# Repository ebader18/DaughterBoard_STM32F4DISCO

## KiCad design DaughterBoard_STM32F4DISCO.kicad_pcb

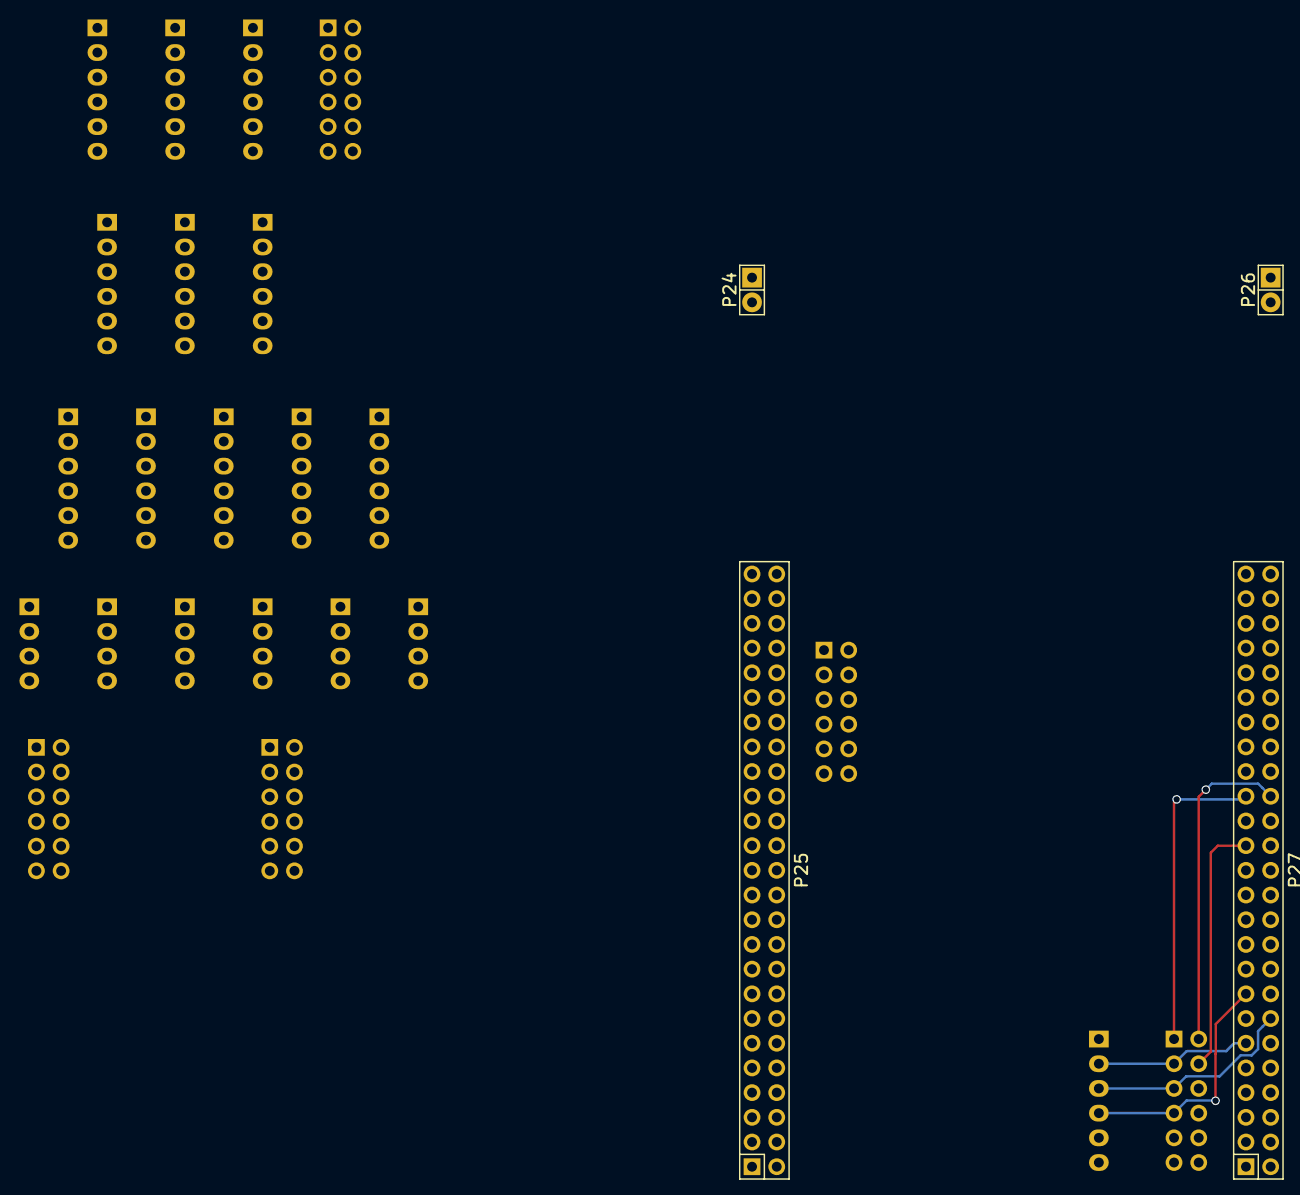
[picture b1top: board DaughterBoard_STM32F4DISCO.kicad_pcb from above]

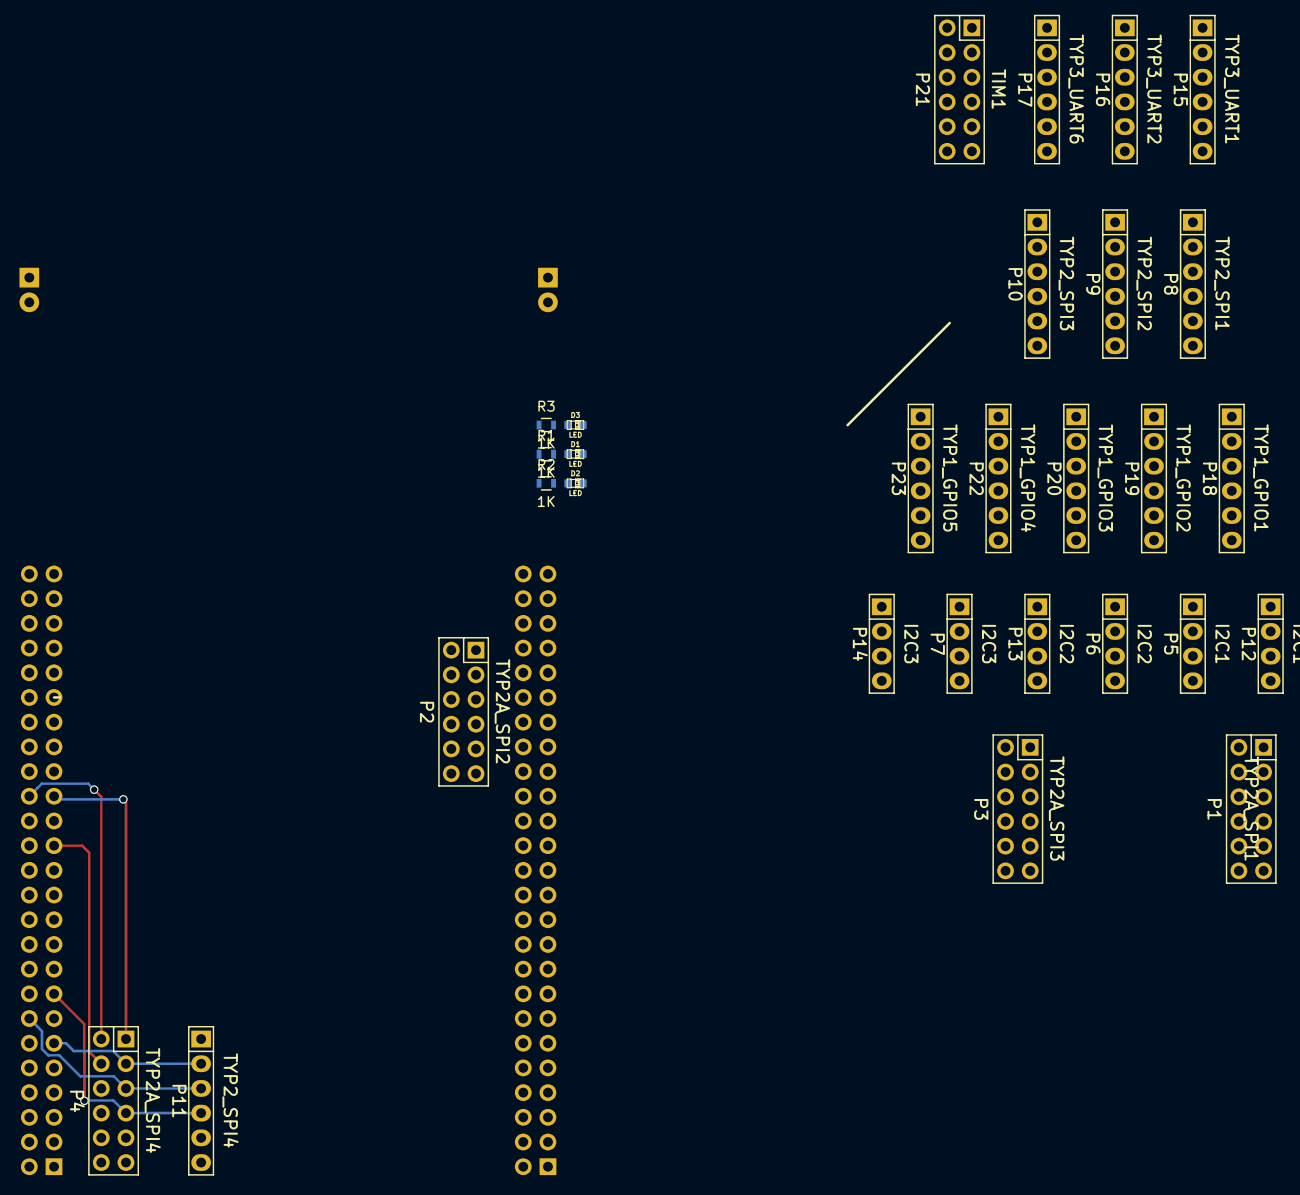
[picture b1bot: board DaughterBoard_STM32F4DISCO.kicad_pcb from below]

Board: 2 copper layers, 33 parts (29 on the bottom side), 77 nets.

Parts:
D1, D2, D3: LED; LED-0603
P1: TYP2A_SPI1; Socket_Strip_Straight_2x06
P2: TYP2A_SPI2; Socket_Strip_Straight_2x06
P3: TYP2A_SPI3; Socket_Strip_Straight_2x06
P4: TYP2A_SPI4; Socket_Strip_Straight_2x06
P5, P12: I2C1; Socket_Strip_Straight_1x04
P6, P13: I2C2; Socket_Strip_Straight_1x04
P7, P14: I2C3; Socket_Strip_Straight_1x04
P8: TYP2_SPI1; Socket_Strip_Straight_1x06
P9: TYP2_SPI2; Socket_Strip_Straight_1x06
P10: TYP2_SPI3; Socket_Strip_Straight_1x06
P11: TYP2_SPI4; Socket_Strip_Straight_1x06
P15: TYP3_UART1; Socket_Strip_Straight_1x06
P16: TYP3_UART2; Socket_Strip_Straight_1x06
P17: TYP3_UART6; Socket_Strip_Straight_1x06
P18: TYP1_GPIO1; Socket_Strip_Straight_1x06
P19: TYP1_GPIO2; Socket_Strip_Straight_1x06
P20: TYP1_GPIO3; Socket_Strip_Straight_1x06
P21: TIM1; Socket_Strip_Straight_2x06
P22: TYP1_GPIO4; Socket_Strip_Straight_1x06
P23: TYP1_GPIO5; Socket_Strip_Straight_1x06
P24, P26: CONN_01X02; Socket_Strip_Straight_1x02
P25, P27: CONN_02X25; Socket_Strip_Straight_2x25
R1, R2, R3: 1K; R_0603

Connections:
/3V: P1.11, P1.12, P2.11, P2.12, P3.11, P3.12, P4.11, P4.12, P5.4, P6.4, P7.4, P8.6, P9.6, P10.6, P11.6, P12.4, P13.4, P14.4, P15.6, P16.6, P17.6, P18.6, P19.6, P20.6, P21.11, P21.12, P22.6, P23.6, P27.5, P27.6, R2.1
/5V: P27.3, P27.4, R1.1
/GND: D1.2, D2.2, D3.2, P1.9, P1.10, P2.9, P2.10, P3.9, P3.10, P4.9, P4.10, P5.3, P6.3, P7.3, P8.5, P9.5, P10.5, P11.5, P12.3, P13.3, P14.3, P15.5, P16.5, P17.5, P18.5, P19.5, P20.5, P21.9, P21.10, P22.5, P23.5, P24.1, P24.2, P25.1, P25.2, P25.5, P25.23, P25.49, P25.50, P26.1, P26.2, P27.1, P27.2, P27.49, P27.50
/PA0: P18.1, P25.12
/PA1: P18.2, P25.11
/PA2: P18.3, P25.14
/PA3: P18.4, P25.13
/PA4: P19.1, P25.16
/PA5: P1.7, P8.4, P25.15
/PA6: P1.5, P8.3, P25.18
/PA7: P19.2, P25.17
/PA8: P7.1, P14.1, P27.43
/PA9: P15.4, P27.44
/PA10: P15.3, P27.41
/PB0: P19.3, P25.22
/PB1: P19.4, P25.21
/PB3: P6.2, P13.2, P27.28
/PB5: P1.3, P8.2, P27.26
/PB6: P23.4, P27.23
/PB7: P1.6, P27.24
/PB8: P5.1, P12.1, P27.19
/PB9: P5.2, P12.2, P27.20
/PB10: P6.1, P13.1, P25.34
/PB12: P11.1, P25.36
/PB13: P2.7, P9.4, P25.37
/PB14: P2.5, P9.3, P25.38
/PB15: P2.3, P9.2
/PC0: P20.1, P25.8
/PC1: P20.2, P25.7
/PC2: P20.3, P25.10
/PC3: P20.4, P25.9
/PC4: P9.1, P25.20
/PC5: P10.1, P25.19
/PC6: P17.4, P27.47
/PC7: P17.3, P27.48
/PC8: P23.2, P27.45
/PC9: P7.2, P14.2, P27.46
/PC10: P3.7, P10.4, P27.37
/PC11: P3.5, P10.3, P27.38
/PC12: P3.3, P10.2, P27.35
/PC13: P1.4, P27.12
/PD0: P3.2, P27.36
/PD1: P3.4, P27.33
/PD2: P23.3, P27.34
/PD3: P4.1, P27.31
/PD4: P4.2, P27.32
/PD5: P16.4, P27.29
/PD6: P16.3, P27.30
/PD7: P4.4, P27.27
/PD8: P2.1, P25.40
/PD9: P2.2, P25.41
/PD10: P2.4, P25.42
/PD11: P3.1, P25.43
/PD12: P22.1, P25.44
/PD13: P22.2, P25.45
/PD14: P22.3, P25.46
/PD15: P22.4, P25.47
/PE0: P2.6, P27.17
/PE1: P8.1, P27.18
/PE2: P4.7, P11.4, P27.15
/PE3: P1.1, P27.16
/PE4: P1.2, P27.13
/PE5: P4.5, P11.3, P27.14
/PE6: P4.3, P11.2, P27.11
/PE7: P21.7, P25.25
/PE8: P21.2, P25.26
/PE9: P21.1, P25.27
/PE10: P21.4, P25.28
/PE11: P21.3, P25.29
/PE12: P21.6, P25.30
/PE13: P21.5, P25.31
/PE14: P23.1, P25.32
/PE15: P21.8, P25.33, P25.39
/VDD: P25.3, P25.4, P27.22, R3.1
unnamed: D1.1, R1.2
unnamed: D2.1, R2.2
unnamed: D3.1, R3.2

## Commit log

2015-02-16 :boom::camel: Added .gitattributes & .gitignore files
2015-02-16 This is the first comit
2015-02-16 Added resources
2015-02-16 Schematic complete Layout placement half done.
2015-02-20 Added a few resources
